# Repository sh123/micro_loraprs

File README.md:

# Arduino Micro LoRA/FSK KISS modem and APRS AX.25 digirepeater

## Introduction
This project is Arduino Micro LoRA/FSK USB KISS modem and standalone APRS AX.25 digirepeater with RA-01 LoRA module. 

Probably, could be easily used with other Arduino boards.

Currently, default radio module is SX1278, such as RA-01/RA-02.

Can be build in two modes:
- As USB KISS LoRA/FSK modem, to be used with Linux AX.25 tools over USB or with APRSDroid or Codec2Talkie applications over USB OTG
- As a standalone LoRA/FSK AX.25 digirepeater optimized for low power consumption

## Configure
Update `include/config.h` with your LoRA modulation settings and module pinouts.

## Build
Use platformio to build required configuration for repeater or modem.

## Photos

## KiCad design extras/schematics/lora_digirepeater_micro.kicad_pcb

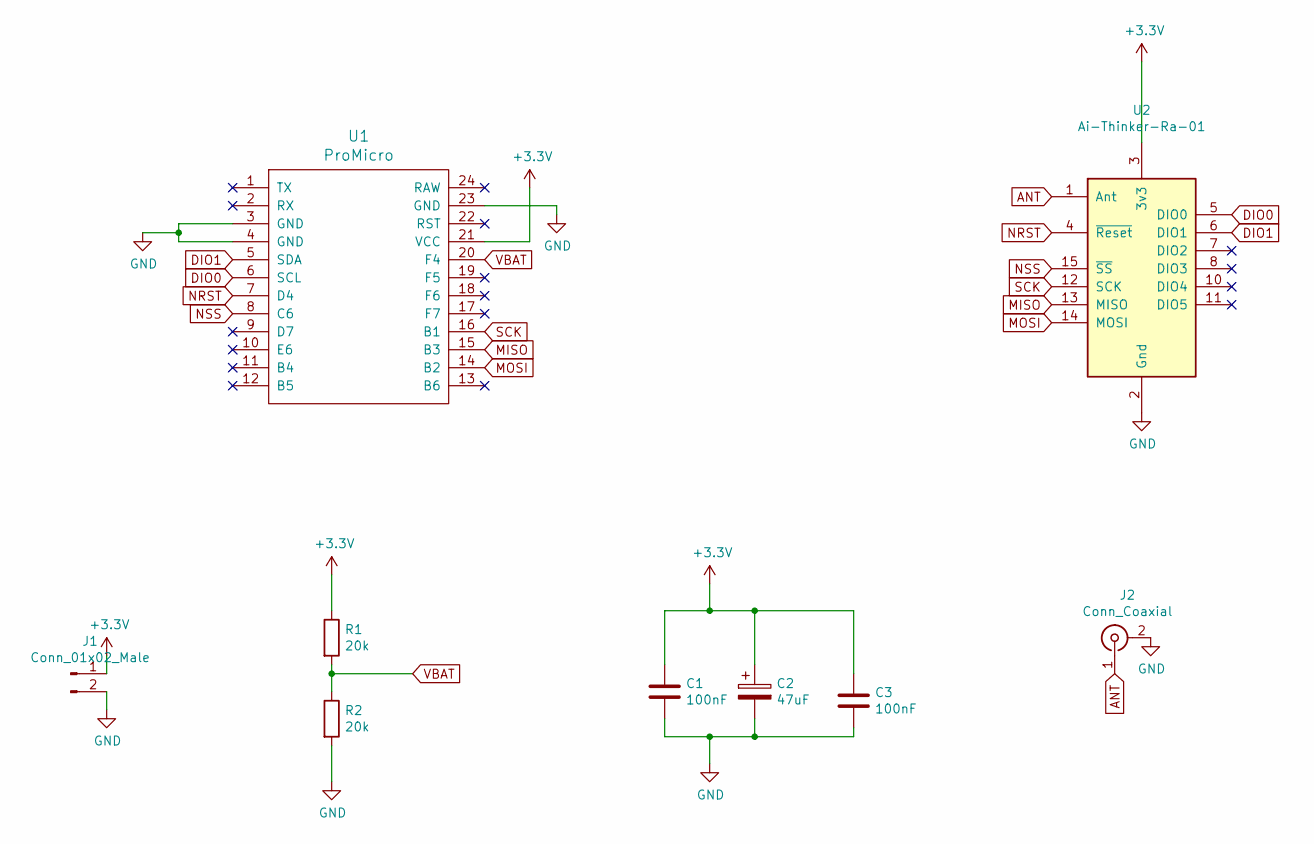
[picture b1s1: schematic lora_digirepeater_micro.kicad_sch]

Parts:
C1, C3: 100nF; C_0805_2012Metric_Pad1.18x1.45mm_HandSolder
C2: 47uF; CP_EIA-7132-28_AVX-C_Pad2.72x3.50mm_HandSolder
J1: Conn_01x02_Male; PinSocket_1x02_P2.54mm_Vertical
J2: Conn_Coaxial; SMA_Samtec_SMA-J-P-X-ST-EM1_EdgeMount
R1, R2: 20k; R_0805_2012Metric_Pad1.20x1.40mm_HandSolder
U1: ProMicro; ProMicro-NoSilk
U2: Ai-Thinker-Ra-01; Ai-Thinker-Ra-01-LoRa

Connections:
+3V3: C1.1, C2.1, C3.1, J1.1, R1.1, U1.21 (VCC), U2.3 (3v3)
ANT: J2.1 (In), U2.1 (Ant)
DIO0: U1.6 (SCL), U2.5 (DIO0)
DIO1: U1.5 (SDA), U2.6 (DIO1)
GND: C1.2, C2.2, C3.2, J1.2, J2.2 (Ext), R2.2, U1.3 (GND), U1.4 (GND), U1.23 (GND), U2.2 (Gnd), U2.9 (Gnd), U2.16 (Gnd)
MISO: U1.15 (B3), U2.13 (MISO)
MOSI: U1.14 (B2), U2.14 (MOSI)
NRST: U1.7 (D4), U2.4 (~Reset)
NSS: U1.8 (C6), U2.15 (~SS)
SCK: U1.16 (B1), U2.12 (SCK)
VBAT: R1.2, R2.1, U1.20 (F4)

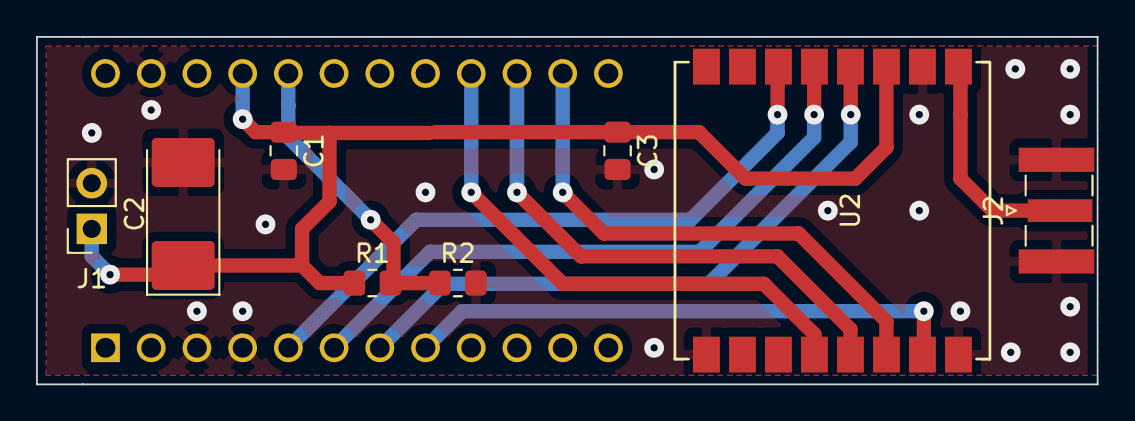
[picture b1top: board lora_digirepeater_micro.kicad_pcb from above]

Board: 2 copper layers, 58.9 x 19.3 mm, 9 parts (0 on the bottom side), 11 nets.

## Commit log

2023-03-12 Added files
2023-03-12 Added missing files
2023-03-12 Move confiig to separate file add debug config
2023-03-13 Add support for set hardware command form c2t
2023-03-13 Added endian.h file
2023-03-13 Comments
2023-03-13 Set hardware fixes
2023-03-15 Allow to specify preamble length
2023-03-17 Added cad files
2023-03-17 Update config
2023-11-18 Fsk support
2023-11-18 Updated set hardware command
2023-11-18 Optimize flash usage
2023-11-18 Compiler messages for modulation type
2023-11-18 Cosmetic changes
2025-03-22 Restrict power ranges and add failure led blinking loop to diagnose modem init failure
